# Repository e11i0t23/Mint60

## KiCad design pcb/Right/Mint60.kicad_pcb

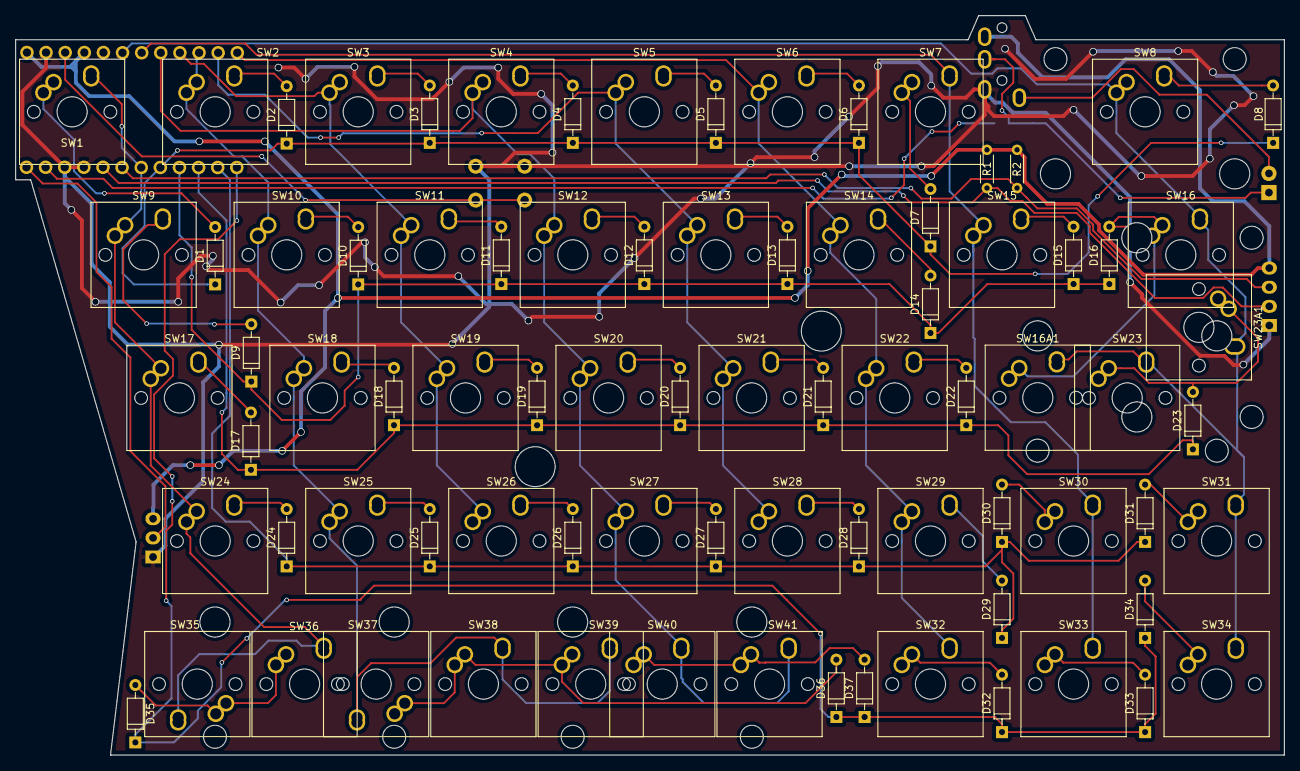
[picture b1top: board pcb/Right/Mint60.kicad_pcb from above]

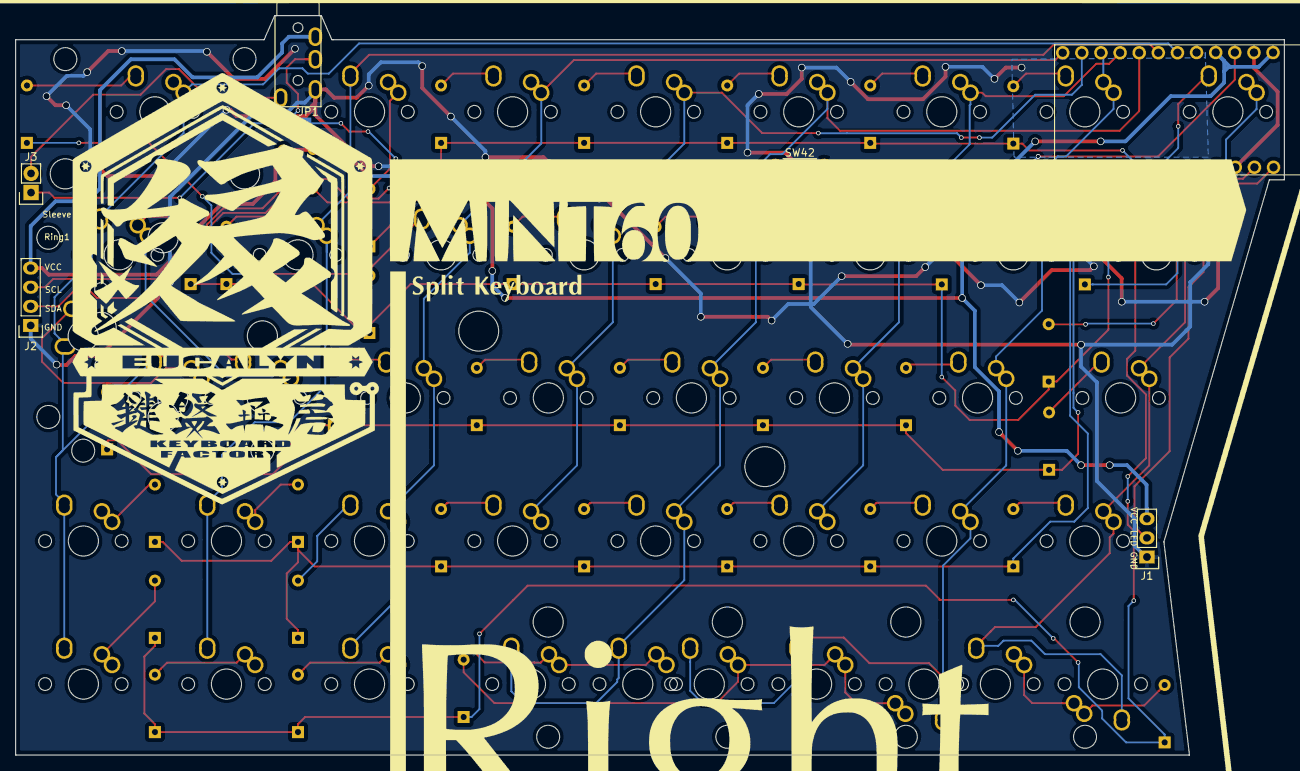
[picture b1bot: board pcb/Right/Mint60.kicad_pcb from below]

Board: 2 copper layers, 168.5 x 98.2 mm, 89 parts (6 on the bottom side), 59 nets.

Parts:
D1, D2, D3, D4, D5, D6, D7, D8, D9, D10, D11, D12, D13, D14, D15, D16, D17, D18, D19, D20, D21, D22, D23, D24, D25, D26, D27, D28, D29, D30, D31, D32, D33, D34, D35, D36, D37: D; Diode
J1: Conn_01x03; Pin_Header_Straight_1x03
J2: Conn_01x04; Pin_Header_Straight_1x04
J3: Conn_01x02; Pin_Header_Straight_1x02
J4: MJ-4PP-9; TRRS_JACK_MJ4PP9_fr
JP1: Jumper_NC_Small; JumperClose
R1, R2: R; R_Axial_DIN0204_L3.6mm_D1.6mm_P5.08mm_Horizontal
SW1, SW2, SW3, SW4, SW5, SW6, SW7, SW9, SW10, SW11, SW12, SW13, SW14, SW15, SW16, SW16A1, SW17, SW18, SW19, SW20, SW21, SW22, SW24, SW25, SW26, SW27, SW28, SW29, SW30, SW31, SW32, SW33, SW34, SW35, SW37, SW38, SW39, SW41: SW_Push; SW_Cherry_Matias_1.00u_PCB
SW8, SW23A1: SW_Push; SW_Cherry_Matias_2.00u_PCB
SW23, SW36, SW40: SW_Push; SW_Cherry_Matias_2.00u_PCB-flip
SW42: SW_Push; SW_PUSH_6mm
U1: ProMicro; ProMicro-Flip

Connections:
+5V: J1.3, J2.4, J4.3, R1.1, R2.2, U1.21, U1.24
Col0: SW1.1, SW9.2, SW17.2, SW24.2, SW35.1, SW36.1, U1.7
Col1: SW2.2, SW10.2, SW18.2, SW25.2, SW37.1, SW38.1, SW39.1, U1.15
Col2: SW3.2, SW11.2, SW19.2, SW26.2, U1.16
Col3: SW4.2, SW12.2, SW20.2, SW27.2, SW40.1, SW41.1, U1.17
Col4: SW5.2, SW13.2, SW21.2, SW28.2, U1.14
Col5: SW6.2, SW14.2, SW22.2, SW29.2, SW32.1, U1.13
Col6: SW7.1, SW15.2, SW30.1, SW33.1, U1.18
Col7: SW8.2, SW16.1, SW16A1.1, SW23.1, SW23A1.1, SW31.1, SW34.1, U1.19
Data: JP1.1, U1.2
GND: J1.1, J2.1, J4.1, SW42.2, U1.3, U1.4, U1.23
LED: J1.2, U1.1
unnamed: D1.2, SW1.2
unnamed: D2.2, SW2.1
unnamed: D3.2, SW3.1
unnamed: D4.2, SW4.1
unnamed: D5.2, SW5.1
unnamed: D6.2, SW6.1
unnamed: D7.2, SW7.2
unnamed: D8.2, SW8.1
unnamed: D9.2, SW9.1
unnamed: D10.2, SW10.1
unnamed: D11.2, SW11.1
unnamed: D12.2, SW12.1
unnamed: D13.2, SW13.1
unnamed: D14.2, SW14.1
unnamed: D15.2, SW15.1
unnamed: D16.2, SW16.2, SW16A1.2
unnamed: D17.2, SW17.1
unnamed: D18.2, SW18.1
unnamed: D19.2, SW19.1
unnamed: D20.2, SW20.1
unnamed: D21.2, SW21.1
unnamed: D22.2, SW22.1
unnamed: D23.2, SW23.2, SW23A1.2
unnamed: D24.2, SW24.1
unnamed: D25.2, SW25.1
unnamed: D26.2, SW26.1
unnamed: D27.2, SW27.1
unnamed: D28.2, SW28.1
unnamed: D29.2, SW29.1
unnamed: D30.2, SW30.2
unnamed: D31.2, SW31.2
unnamed: D32.2, SW32.2
unnamed: D33.2, SW33.2
unnamed: D34.2, SW34.2
unnamed: D35.2, SW35.2, SW36.2
unnamed: D36.2, SW37.2, SW38.2, SW39.2
unnamed: D37.2, SW40.2, SW41.2
unnamed: J3.1, J4.2, JP1.2
unnamed: J3.2, J4.4
Reset: SW42.1, U1.22
Row0: D1.1, D2.1, D3.1, D4.1, D5.1, D6.1, D7.1, D8.1, U1.8
Row1: D9.1, D10.1, D11.1, D12.1, D13.1, D14.1, D15.1, D16.1, U1.9
Row2: D17.1, D18.1, D19.1, D20.1, D21.1, D22.1, D23.1, U1.10
Row3: D24.1, D25.1, D26.1, D27.1, D28.1, D29.1, D30.1, D31.1, U1.11
Row4: D32.1, D33.1, D34.1, D35.1, D36.1, D37.1, U1.12
SCL: J2.3, R2.1, U1.6
SDA: J2.2, R1.2, U1.5

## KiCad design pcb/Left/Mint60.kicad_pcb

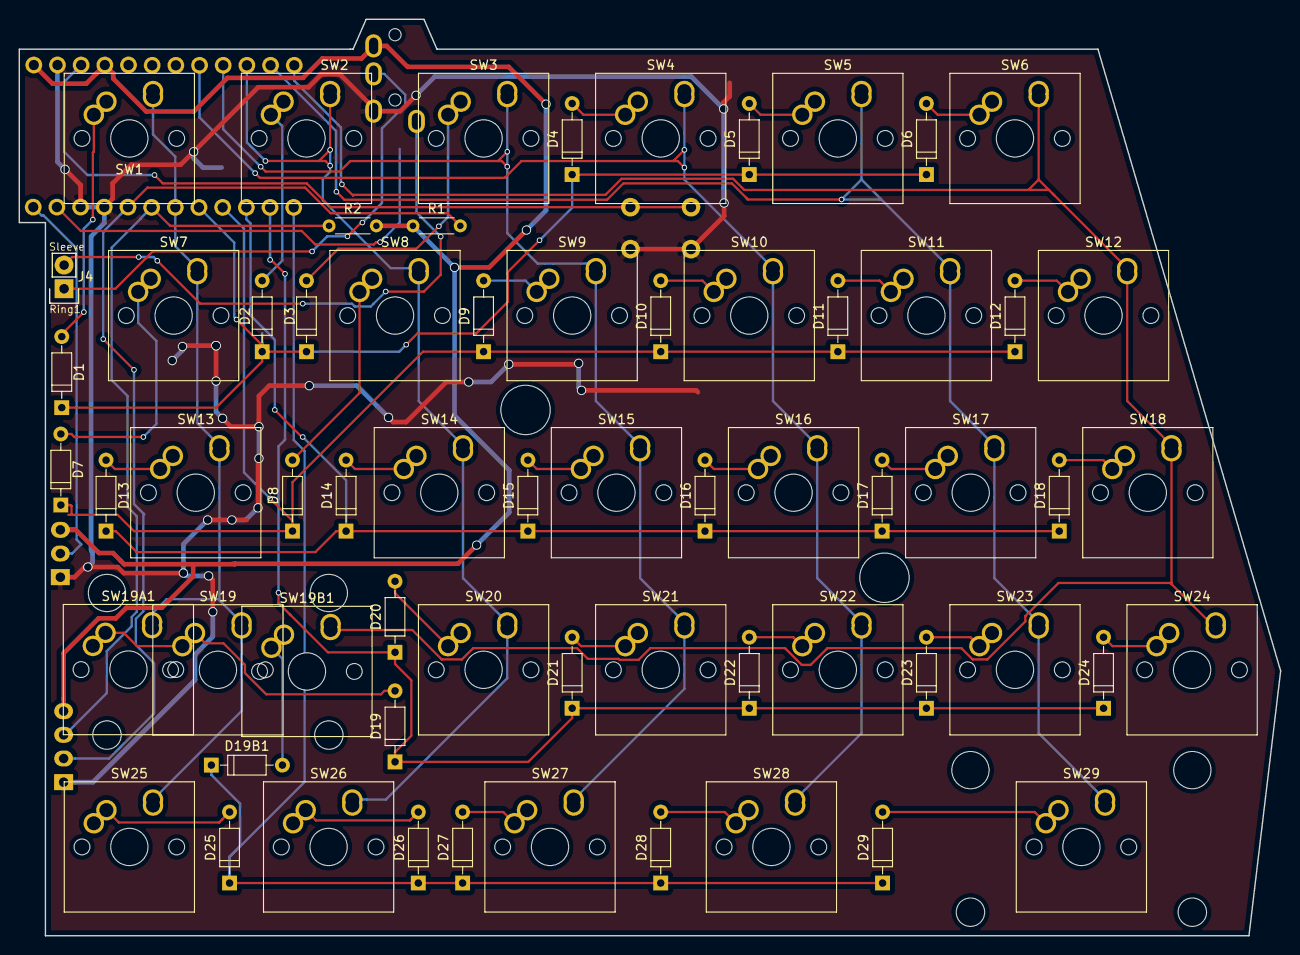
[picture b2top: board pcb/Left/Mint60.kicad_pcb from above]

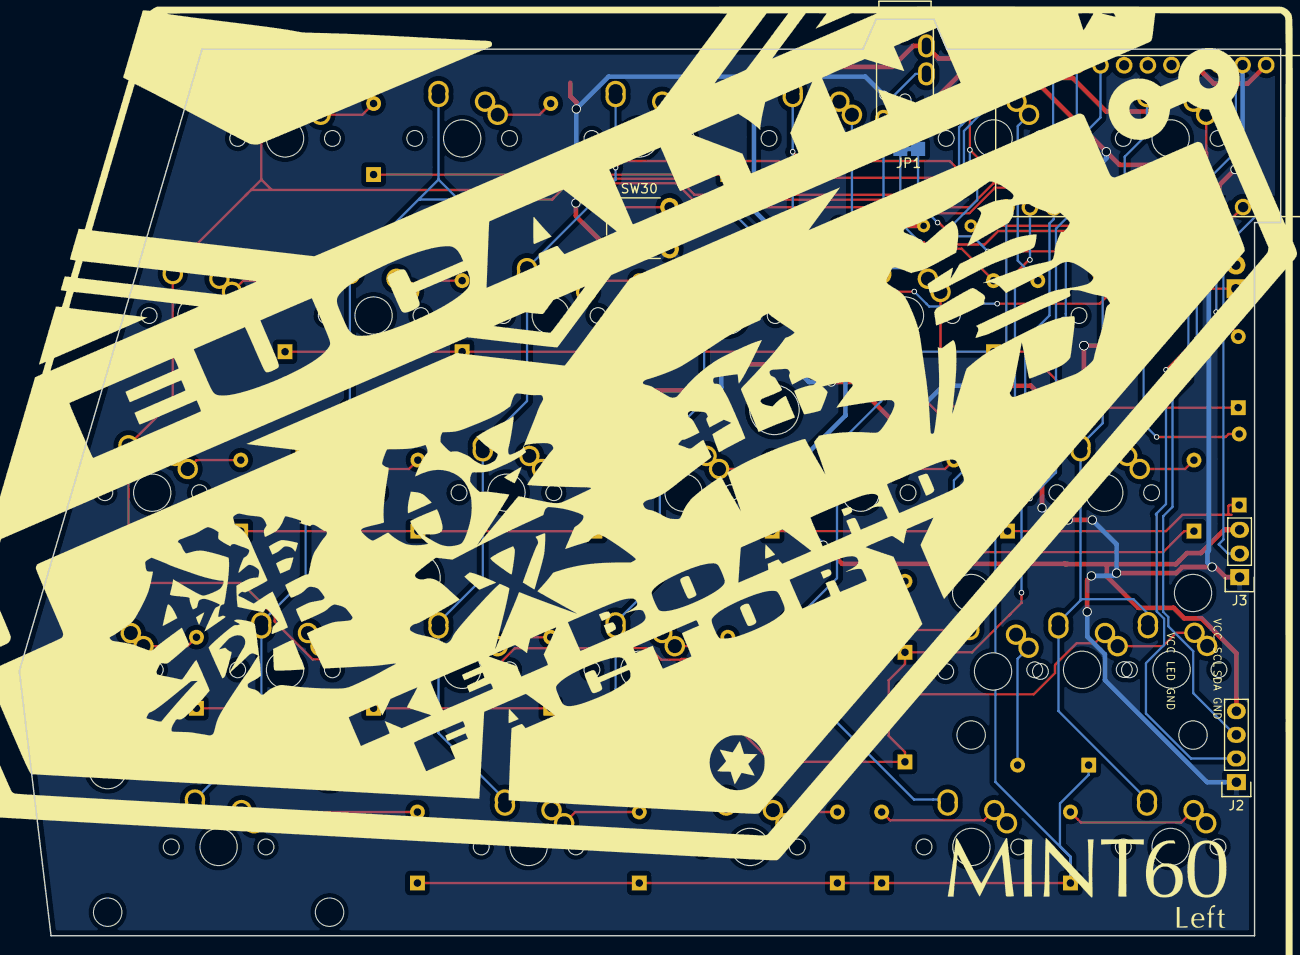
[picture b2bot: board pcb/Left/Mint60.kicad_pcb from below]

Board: 2 copper layers, 135.3 x 98.3 mm, 70 parts (5 on the bottom side), 50 nets.

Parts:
D1, D2, D3, D4, D5, D6, D7, D8, D9, D10, D11, D12, D13, D14, D15, D16, D17, D18, D19, D19B1, D20, D21, D22, D23, D24, D25, D26, D27, D28, D29: D; Diode
J1: MJ-4PP-9; TRRS_JACK_MJ4PP9_fr
J2: Conn_01x04; Pin_Header_Straight_1x04
J3: Conn_01x03; Pin_Header_Straight_1x03
J4: Conn_01x02; Pin_Header_Straight_1x02
JP1: Jumper_NC_Small; JumperClose
R1, R2: R; R_Axial_DIN0204_L3.6mm_D1.6mm_P5.08mm_Horizontal
SW1, SW2, SW3, SW4, SW5, SW6, SW7, SW8, SW9, SW10, SW11, SW12, SW13, SW14, SW15, SW16, SW17, SW18, SW19A1, SW19B1, SW20, SW21, SW22, SW23, SW24, SW25, SW26, SW27, SW28: SW_Push; SW_Cherry_Matias_1.00u_PCB
SW19, SW29: SW_Push; SW_Cherry_Matias_2.00u_PCB-flip
SW30: SW_Push; SW_PUSH_6mm
U1: ProMicro; ProMicro-Flip

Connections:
+5V: J1.3, J2.4, J3.3, R1.1, R2.2, U1.21, U1.24
Col0: SW1.1, SW7.1, SW13.1, SW19.1, SW19A1.1, SW25.1, U1.7
Col1: SW2.1, SW8.1, SW14.1, SW20.1, SW26.1, U1.15
Col2: SW3.1, SW9.1, SW15.1, SW21.1, SW27.1, U1.16
Col3: SW4.1, SW10.1, SW16.1, SW22.1, SW28.1, U1.17
Col4: SW5.1, SW11.1, SW17.1, SW23.1, SW29.1, U1.14
Col5: SW6.1, SW12.1, SW18.1, SW19B1.1, SW24.1, U1.13
Data: JP1.1, U1.2
GND: J1.1, J2.1, J3.1, SW30.2, U1.3, U1.4, U1.23
LED: J3.2, U1.1
unnamed: D1.2, SW1.2
unnamed: D2.2, SW2.2
unnamed: D3.2, SW3.2
unnamed: D4.2, SW4.2
unnamed: D5.2, SW5.2
unnamed: D6.2, SW6.2
unnamed: D7.2, SW7.2
unnamed: D8.2, SW8.2
unnamed: D9.2, SW9.2
unnamed: D10.2, SW10.2
unnamed: D11.2, SW11.2
unnamed: D12.2, SW12.2
unnamed: D13.2, SW13.2
unnamed: D14.2, SW14.2
unnamed: D15.2, SW15.2
unnamed: D16.2, SW16.2
unnamed: D17.2, SW17.2
unnamed: D18.2, SW18.2
unnamed: D19.2, SW19.2, SW19A1.2
unnamed: D19B1.2, SW19B1.2
unnamed: D20.2, SW20.2
unnamed: D21.2, SW21.2
unnamed: D22.2, SW22.2
unnamed: D23.2, SW23.2
unnamed: D24.2, SW24.2
unnamed: D25.2, SW25.2
unnamed: D26.2, SW26.2
unnamed: D27.2, SW27.2
unnamed: D28.2, SW28.2
unnamed: D29.2, SW29.2
unnamed: J1.2, J4.1, JP1.2
unnamed: J1.4, J4.2
Reset: SW30.1, U1.22
Row0: D1.1, D2.1, D3.1, D4.1, D5.1, D6.1, U1.8
Row1: D7.1, D8.1, D9.1, D10.1, D11.1, D12.1, U1.9
Row2: D13.1, D14.1, D15.1, D16.1, D17.1, D18.1, U1.10
Row3: D19.1, D20.1, D21.1, D22.1, D23.1, D24.1, U1.11
Row4: D19B1.1, D25.1, D26.1, D27.1, D28.1, D29.1, U1.12
SCL: J2.3, R2.1, U1.6
SDA: J2.2, R1.2, U1.5

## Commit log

2020-06-16 gerbers and case update
